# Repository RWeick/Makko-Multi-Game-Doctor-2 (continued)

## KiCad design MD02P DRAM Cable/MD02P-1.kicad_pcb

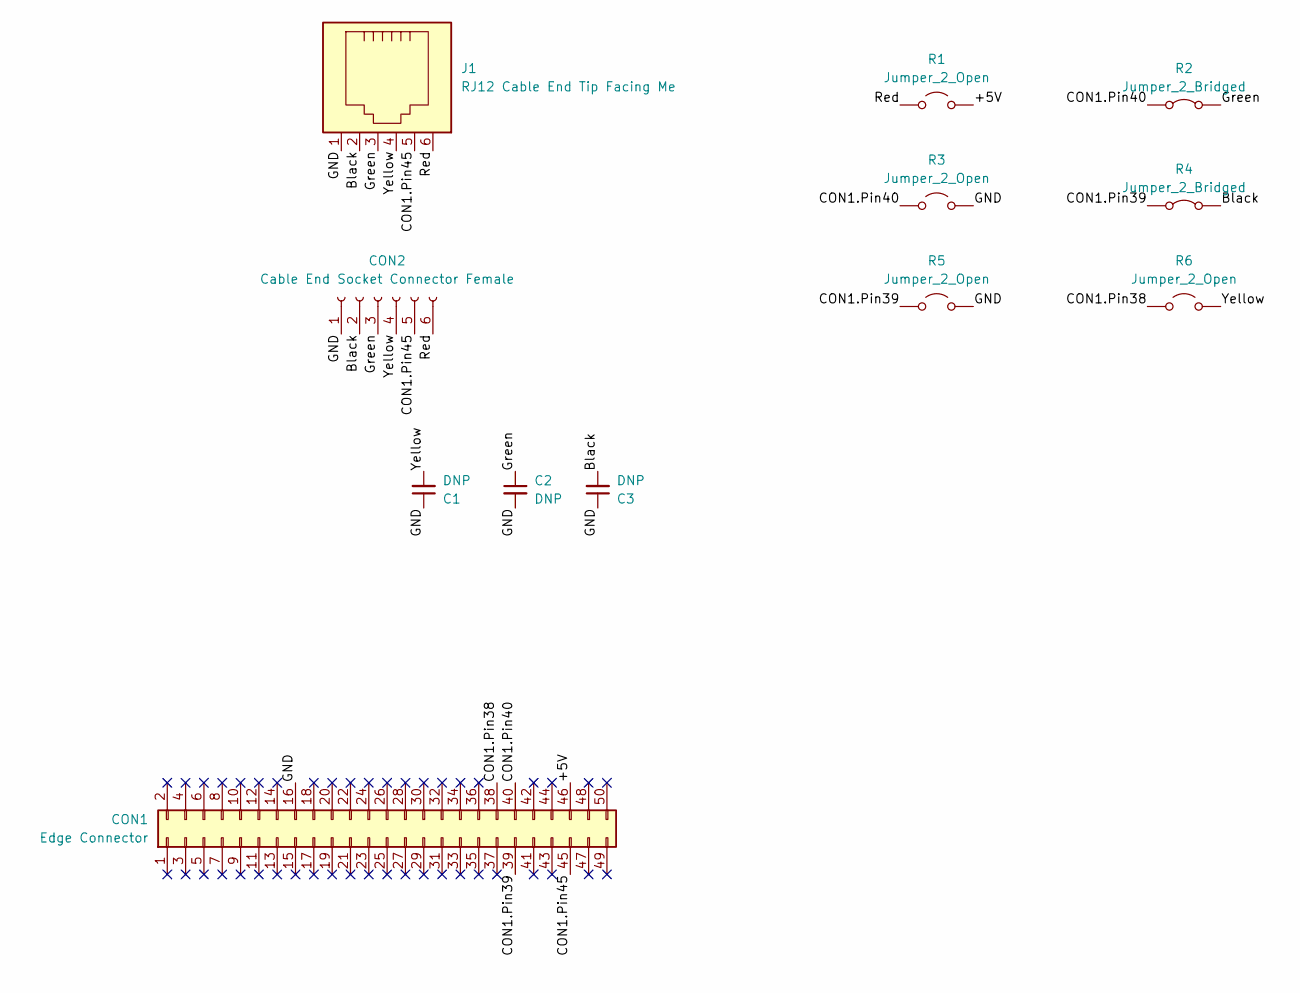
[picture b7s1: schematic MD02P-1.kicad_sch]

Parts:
C1, C2, C3: DNP; C_Disc_D5.0mm_W2.5mm_P2.50mm
CON1: Edge Connector
CON2: Cable End Socket Connector Female; PinHeader_1x06_P2.54mm_Vertical
J1: RJ12 Cable End Tip Facing Me
R1, R3, R5, R6: Jumper_2_Open; R_Axial_DIN0207_L6.3mm_D2.5mm_P10.16mm_Horizontal
R2, R4: Jumper_2_Bridged; R_Axial_DIN0207_L6.3mm_D2.5mm_P10.16mm_Horizontal

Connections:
/+5V: CON1.46, R1.2 (B)
/Black: C3.2, CON2.2, J1.2, R4.2 (B)
/CON1.Pin38: CON1.38, R6.1 (A)
/CON1.Pin39: CON1.39, R4.1 (A), R5.1 (A)
/CON1.Pin40: CON1.40, R2.1 (A), R3.1 (A)
/CON1.Pin45: CON1.45, CON2.5, J1.5
/GND: C1.1, C2.2, C3.1, CON1.16, CON2.1, J1.1, R3.2 (B), R5.2 (B)
/Green: C2.1, CON2.3, J1.3, R2.2 (B)
/Red: CON2.6, J1.6, R1.1 (A)
/Yellow: C1.2, CON2.4, J1.4, R6.2 (B)

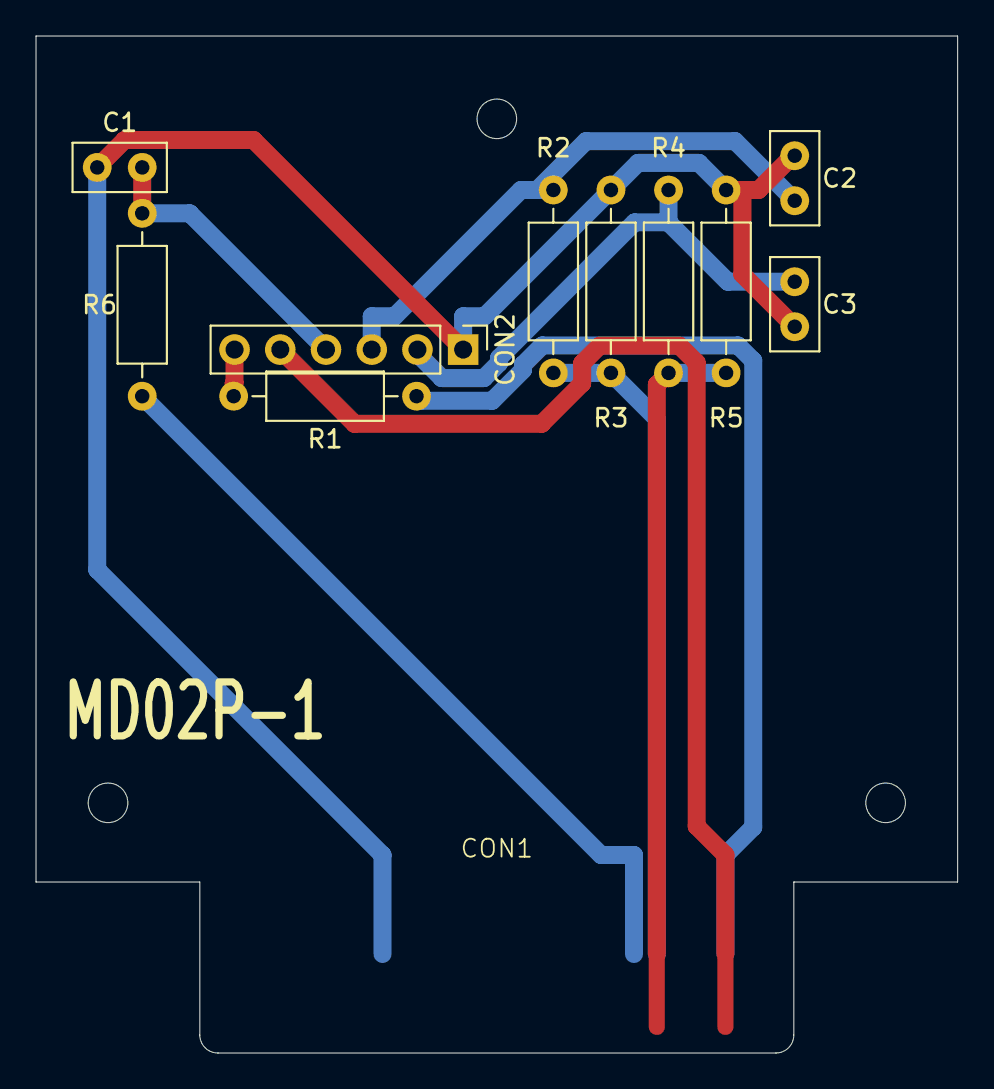
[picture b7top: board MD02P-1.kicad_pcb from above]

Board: 2 copper layers, 51.2 x 56.5 mm, 11 parts (0 on the bottom side), 10 nets.

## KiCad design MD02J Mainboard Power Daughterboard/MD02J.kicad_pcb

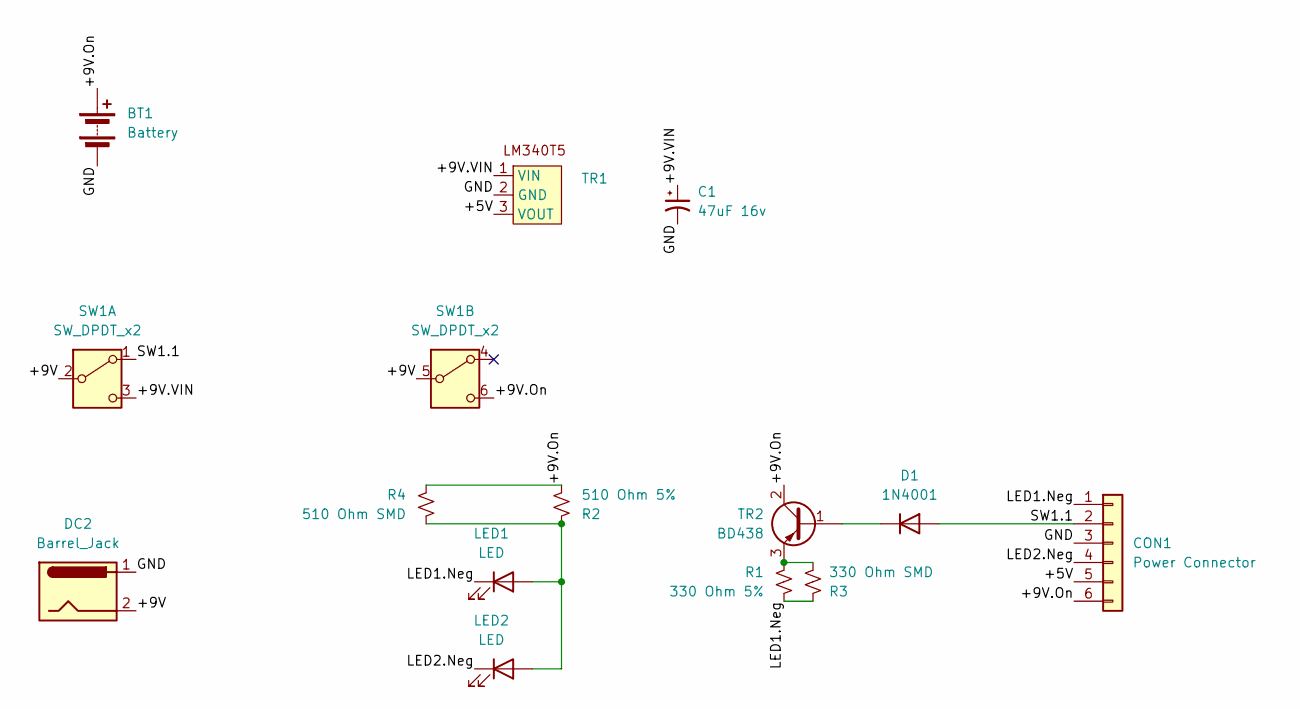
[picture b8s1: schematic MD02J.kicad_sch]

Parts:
BT1: Battery
C1: 47uF 16v; CP_Radial_D5.0mm_P2.50mm
CON1: Power Connector; PinHeader_1x06_P2.54mm_Vertical
D1: 1N4001; D_A-405_P7.62mm_Horizontal
DC2: Barrel_Jack; DC Jack
LED1, LED2: LED; LED_D4.0mm
R1: 330 Ohm 5%; R_Axial_DIN0207_L6.3mm_D2.5mm_P10.16mm_Horizontal
R2: 510 Ohm 5%; R_Axial_DIN0207_L6.3mm_D2.5mm_P10.16mm_Horizontal
R3: 330 Ohm SMD; R_1206_3216Metric
R4: 510 Ohm SMD; R_1206_3216Metric
SW1: SW_DPDT_x2; Slide Switch
TR1: TO-220-3_Horizontal_TabDown
TR2: BD438; TO-220-3_Horizontal_TabDown

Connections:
/+5V: CON1.5, TR1.3 (VOUT)
/+9V: DC2.2, SW1.2 (B), SW1.5 (B)
/+9V.On: BT1.1 (+), CON1.6, R2.2, R4.2, SW1.6 (C), TR2.2 (C)
/+9V.VIN: C1.1, SW1.3 (C), TR1.1 (VIN)
/GND: BT1.2 (-), C1.2, CON1.3, DC2.1, SW1.7, TR1.2 (GND)
/LED1.Neg: CON1.1, LED1.1 (K), R1.2, R3.2
/LED2.Neg: CON1.4, LED2.1 (K)
/SW1.1: CON1.2, D1.2 (A), SW1.1 (A)
unnamed: D1.1 (K), TR2.1 (B)
unnamed: LED1.2 (A), LED2.2 (A), R2.1, R4.1
unnamed: R1.1, R3.1, TR2.3 (E)

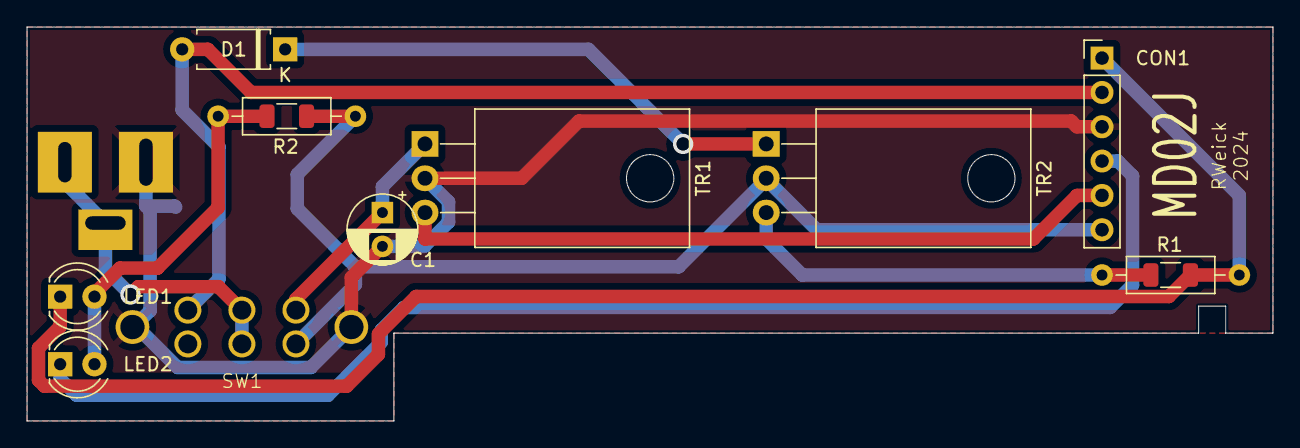
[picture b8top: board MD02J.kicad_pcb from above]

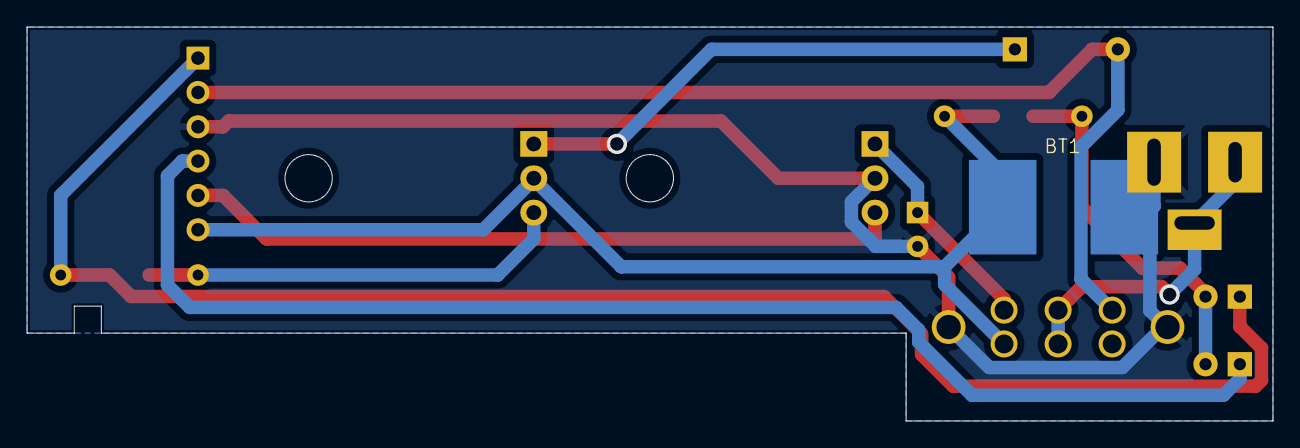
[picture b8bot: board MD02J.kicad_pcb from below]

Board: 2 copper layers, 92.2 x 29.2 mm, 14 parts (2 on the bottom side), 11 nets.
